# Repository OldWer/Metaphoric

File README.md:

# Metaphoric - an enhanced Oric clone
Metaphoric is an Oric clone with the memory subsystem based on the OriClone-1 project and some additional features:
* Composite video output (RCA socket)
* TRRS audio-video socket for connecting "jack to 3xRCA" cable
* Footprints for both original AY-3-8912 chips and for (much cheaper) AY-3-8910 chips (or other 40-pin clones)
* Ability to use 7905 or 7805 power regulator and also to power the Metaphoric using an external +5V power supply
* Two Atari-standard joystick ports on the keyboard PCB — one is an IJK „Stingy” port, the other is a cursors+space joystick for games that do not support IJK but are controlled with cursors or make it possible to redefine the keys.
* Easily accessible RESET and NMI buttons on top of the keyboard.
* Easily accessible switches for changing the ROM between Oric-1 and Oric Atmos and for disabling the IJK interface (it may interfere with the operation of printer port and it can also corrupt sound in games that do not support IJK, e.g. Manic Miner)
* Automatic hardware V-sync hack - original Orics did not have any way of checking the vertical sync signal, which made it difficult to write games without flickering sprites, so somebody came up with the idea of connecting video sync signal to tape in using an external cable and synchronizing games/demos in that way. Metaphoric has a transistor that connects sync out to tape in when the tape relay is inactive and disconnects it when the relay is active (to allow loading from tape).

# Building the Metaphoric
<b>Note</b>: The main PCB fits in the original Oric-1/Atmos case (the keyboard PCB <i>does not</i>!). If you would like to use the main PCB with the original keyboard and case, do not install J10 (TRRS socket) and J7 (auxiliary connector that supports the extra switches, buttons and ports on the keyboard). Also all the chips near the bottom of the board - IC10, IC15/18, IC5, IC6, IC12 and IC16 - cannot be socketed and must be soldered directly to the board, or the original case won't close.

The repository contains two directories with KiCAD projects for the main PCB and the keyboard PCB. The bill of materials is available in <i>BOM.*</i> files in the respective directories (in <i>.csv</i>, <i>.xlsx</i> and <i>.PDF</i> formats). In the <i>gerbers</i> subdirectories there are gerber files ready for manufacturing (I used recommended JLCPCB settings when exporting the gerbers). In the main PCB's <i>STL</i> subdirectory there are 3D models for a simple case and also for a spacer which you can print in 5 copies and which is used to separate the two boards. In the keyboard's <i>STL</i> subdirectory there is a 3D model for a holder that fits in the big square holes in the keyboard PCB and holds a typical space key stabilizer.

<b>Note about ROMs</b>: You can use either a 28c128 EEPROM or a 27c512 EPROM, appropriate <i>.bin</i> files are in the <i>MetaphoricV2/ROM</i> subdirectory. 27c256 EPROM would be enough to store two 16K banks with Oric-1 and Atmos ROMs, but it has different pinout - it would still work, but it wouldn't be possible to select ROM banks and only the high bank would be available. However, if you happen to have only 27c256 EPROMs, you may cut the trace between the ROM pins 27 and 28 (on the back of the PCB) and run a bodge wire from ROM pin 1 to ROM pin 27; this should make it possible to use a 27c256 EPROM with switchable banks.

Most of the build is pretty self-explanatory, as all the components are described on the PCB. The things to watch for, in no particular order, are as follows:
1. You can omit all the parts in the 'COMPOSITE VIDEO SECTION' if you're only planning to use the RGB output (well, maybe except for the TRRS socket, which can also be used to output audio, and the J11 header). The file 'RGB_Scart_Tape.pdf' shows how to build a SCART cable, and this is definitely the recommended way of using an Oric, original or cloned.
2. Next to the composite RCA socket there is the J11 header. You can put jumper on pins 2-3 to use the nearby 3.5mm TRRS socket as an audio/video video out; there are ready-made 3.5mm jack-3 x RCA cables which you can use to output video and sound. Or you can put a jumper on pins 1-2 to use the TRRS socket as a regular 3.5mm stereo sound out, useful for connecting the Oric to a stereo system or an external speaker. 
3. You can omit all the parts in the "AMPLIFIER SECTION" if you're not going to use the internal speaker. Again, highly recommended to skip these components, they were only added for the sake of completeness, the sound quality is pretty terrible with the internal speaker and in some games there is no way to turn it off or to control volume.
4. The J1 header on the right side of the board can be used to switch the ROM bank, but if the main PCB is connected to the Metaphoric keyboard PCB, it <b>should not</b> be jumpered. There is a switch on the keyboard PCB that does the same, and because switching the banks means connecting either ground or +5V to one of the ROM address lines, if you leave the J1 jumpered and then connect the Metaphoric keyboard, in one of the two switch positions the +5V will get shorted to ground. So you can install the J1 e.g. for testing the main PCB or if it is to be used in the original Oric case, but before you connect it to the Metaphoric keyboard, <b>remember to take the jumper off!</b>
5. In the power section in the top right corner of the main PCB there are footprints for either 7905 or 7805 regulator. The 7905 is recommended only if you intend to use the Metaphoric with original Oric accessories, such as floppy drives (or modern recreations, such as Cumana Reborn). Modern solutions, such as Erebus or Loci, can be used with 7805 or an external +5V power supply. Depending on which regulator you choose, you must close one of the J12/J13 bridges. Close J12 (using a piece of wire, a diode leg will do) if using 7905, close J13 if using 7805. It is also possible to connect an external power switch across one of those bridges and use it to power the Metaphoric on and off. Another way to power the Metaphoric is to close both J12 and J13 bridges (without installing any regulator!) and use external +5V power supply, <b>center positive</b> (ground on the sleeve, +5V on the tip). I personally prefer this solution (no heat generated inside) and just use a USB power supply. If you decide to use a regulator, power the Metaphoric with a +9V power supply, <b>center positive</b>.
9. The main PCB and the keyboard PCB are connected using two pin headers - J3 and J7 on the main PCB, J1 and J2 on the keyboard PCB. Two male pin headers must be installed on the back of the main PCB, two female headers on the back of the keyboard PCB, and then the two boards must be connected back to back:

Then you should put 3D printed spacers between the two boards where the holes are and screw the boards to the case using M3x16 or M3x18 screws.

10. As for the keyboard, the joystick ports must be soldered on the back side of the PCB, like so:

11. There are also solder jumpers JP2 and JP3 that can be used to configure additional joystick buttons (as in eg. MSX, Amstrad CPC or Sega Master System/Amiga joysticks). There are some powered joysticks (e.g. with an autofire function) which are usually powered from the pin 7 of the DB9 port, and it probably wouldn't be a good idea to power them intermittently from the outputs of the VIA or the AY chip. If you'd like to use additional buttons, see the note in the keyboard schematic.
12. The spacebar stabilizer holder must be printed once in normal orientation (left) and once mirrored (right), because it is not exactly symmetrical. Then the holders must be pushed into the big square holes in the kyeboard PCB (some light sanding may be necessary), and finally the stabilizer itself must be glued to the holders with a tiny amount of glue (so as not to glue together the moving plastic parts).

If in doubt, open the relevant KiCAD PCB file and go to the 3D viewer; I've added 3D models for all the parts, creating some that I could not find anywhere, and you can check exactly how everything should look like.

If you have any questions, write to me at oldwer@op.pl, I will be happy to help.

Good luck soldering your own Oric!

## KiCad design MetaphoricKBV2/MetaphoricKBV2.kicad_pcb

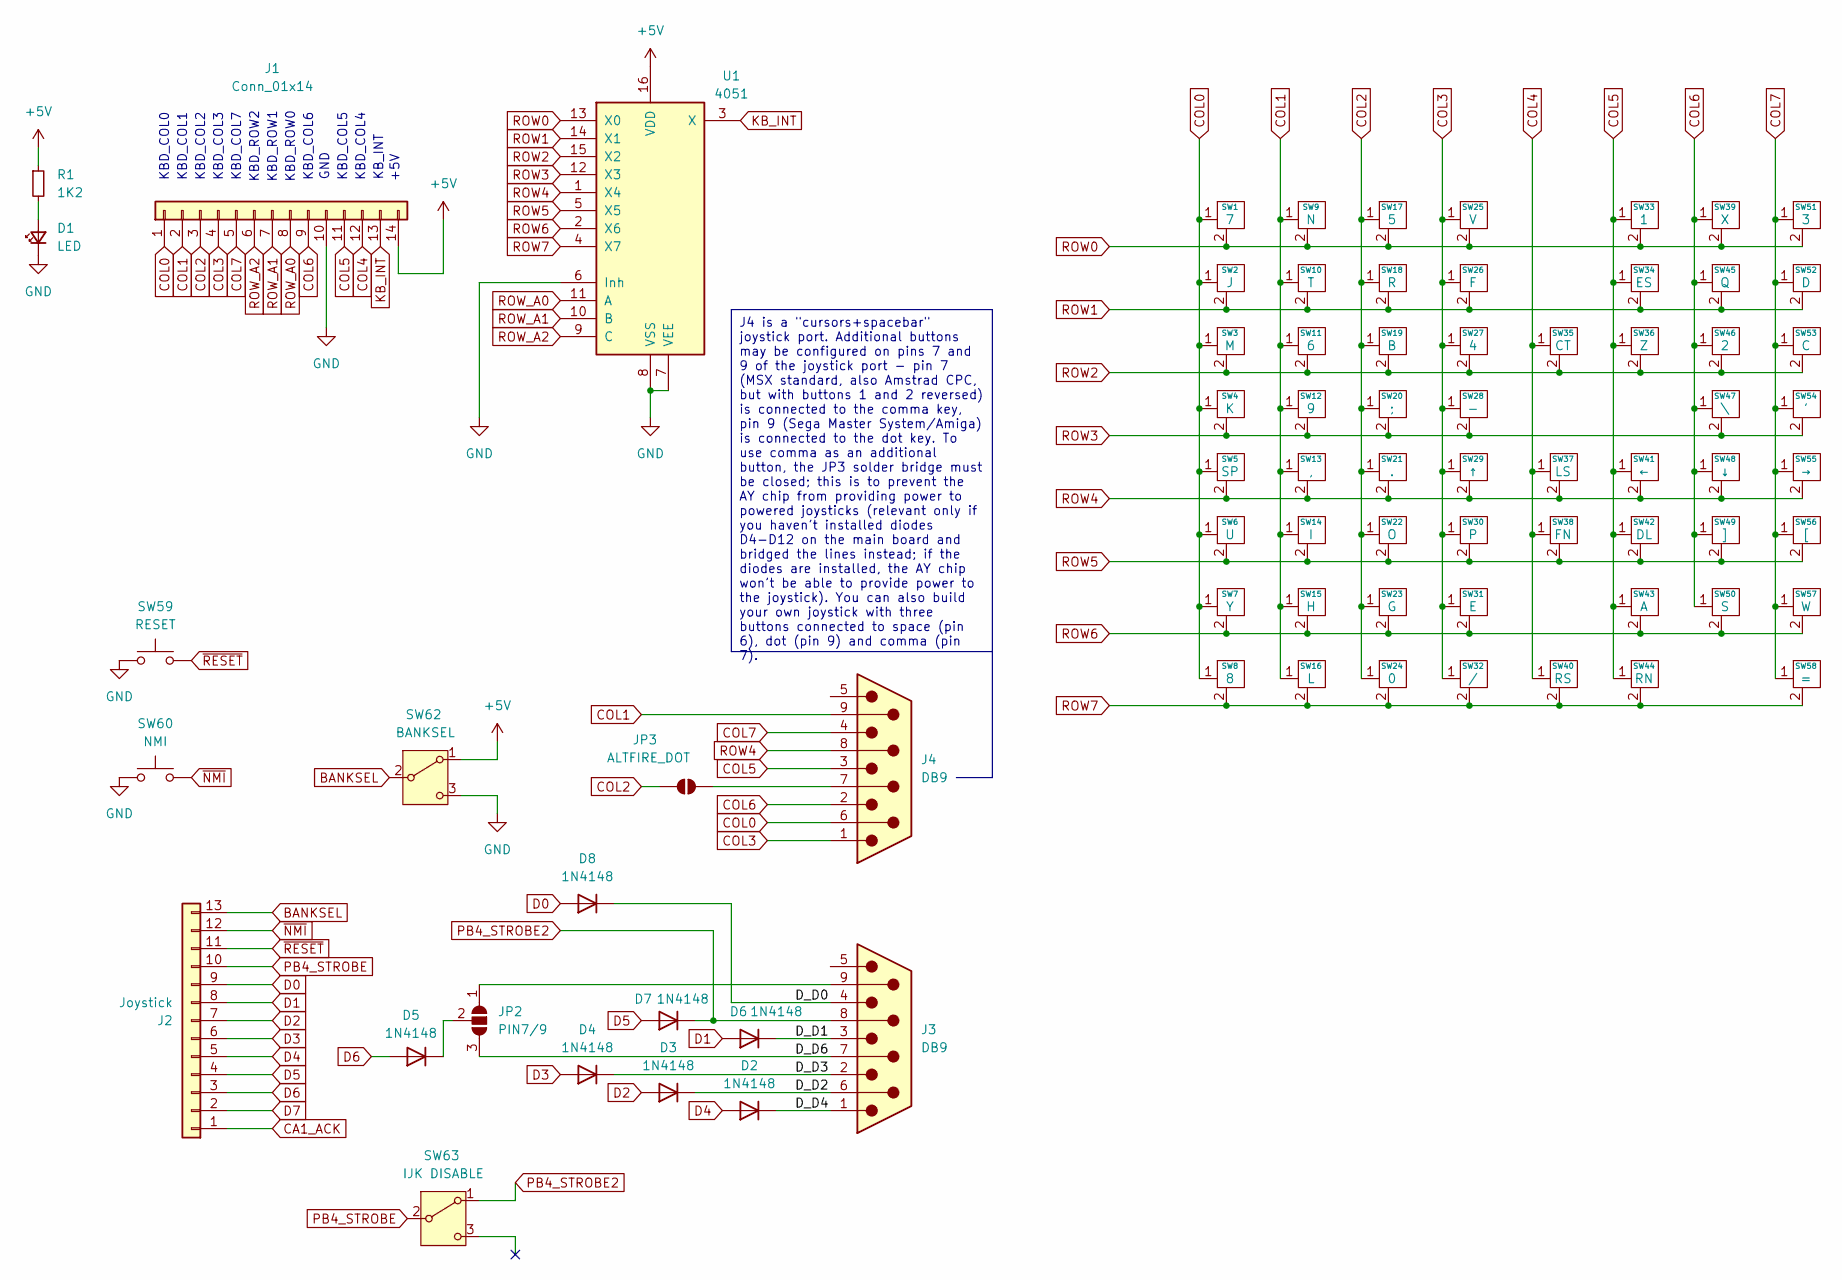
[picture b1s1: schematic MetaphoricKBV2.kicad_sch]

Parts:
D1: LED; LED_D5.0mm
D2, D3, D4, D5, D6, D7, D8: 1N4148; D_DO-35_SOD27_P7.62mm_Horizontal
J1: Conn_01x14; PinHeader_1x14_P2.54mm_Vertical
J2: Joystick; PinHeader_1x13_P2.54mm_Vertical
J3, J4: DB9; DB_9M
JP2: PIN7/9; SolderJumper-3_P1.3mm_Open_RoundedPad1.0x1.5mm
JP3: ALTFIRE_DOT; SolderJumper-2_P1.3mm_Open_RoundedPad1.0x1.5mm
R1: 1K2; R_Axial_DIN0204_L3.6mm_D1.6mm_P7.62mm_Horizontal
SW1: 7; SW_Cherry_MX_PCB_1.00u
SW2: J; SW_Cherry_MX_PCB_1.00u
SW3: M; SW_Cherry_MX_PCB_1.00u
SW4: K; SW_Cherry_MX_PCB_1.00u
SW5: SP; SW_Cherry_MX_PCB_6.25u
SW6: U; SW_Cherry_MX_PCB_1.00u
SW7: Y; SW_Cherry_MX_PCB_1.00u
SW8: 8; SW_Cherry_MX_PCB_1.00u
SW9: N; SW_Cherry_MX_PCB_1.00u
SW10: T; SW_Cherry_MX_PCB_1.00u
SW11: 6; SW_Cherry_MX_PCB_1.00u
SW12: 9; SW_Cherry_MX_PCB_1.00u
SW13: ,; SW_Cherry_MX_PCB_1.00u
SW14: I; SW_Cherry_MX_PCB_1.00u
SW15: H; SW_Cherry_MX_PCB_1.00u
SW16: L; SW_Cherry_MX_PCB_1.00u
SW17: 5; SW_Cherry_MX_PCB_1.00u
SW18: R; SW_Cherry_MX_PCB_1.00u
SW19: B; SW_Cherry_MX_PCB_1.00u
SW20: ;; SW_Cherry_MX_PCB_1.00u
SW21: .; SW_Cherry_MX_PCB_1.00u
SW22: O; SW_Cherry_MX_PCB_1.00u
SW23: G; SW_Cherry_MX_PCB_1.00u
SW24: 0; SW_Cherry_MX_PCB_1.00u
SW25: V; SW_Cherry_MX_PCB_1.00u
SW26: F; SW_Cherry_MX_PCB_1.00u
SW27: 4; SW_Cherry_MX_PCB_1.00u
SW28: -; SW_Cherry_MX_PCB_1.00u
SW29: ↑; SW_Cherry_MX_PCB_1.00u
SW30: P; SW_Cherry_MX_PCB_1.00u
SW31: E; SW_Cherry_MX_PCB_1.00u
SW32: /; SW_Cherry_MX_PCB_1.00u
SW33: 1; SW_Cherry_MX_PCB_1.00u
SW34: ES; SW_Cherry_MX_PCB_1.00u
SW35: CT; SW_Cherry_MX_PCB_1.00u
SW36: Z; SW_Cherry_MX_PCB_1.00u
SW37: LS; SW_Cherry_MX_PCB_1.50u
SW38: FN; SW_Cherry_MX_PCB_1.00u
SW39: X; SW_Cherry_MX_PCB_1.00u
SW40: RS; SW_Cherry_MX_PCB_1.50u
SW41: ←; SW_Cherry_MX_PCB_1.00u
SW42: DL; SW_Cherry_MX_PCB_1.00u
SW43: A; SW_Cherry_MX_PCB_1.00u
SW44: RN; SW_Cherry_MX_PCB_1.50u
SW45: Q; SW_Cherry_MX_PCB_1.00u
SW46: 2; SW_Cherry_MX_PCB_1.00u
SW47: \; SW_Cherry_MX_PCB_1.00u
SW48: ↓; SW_Cherry_MX_PCB_1.00u
SW49: ]; SW_Cherry_MX_PCB_1.00u
SW50: S; SW_Cherry_MX_PCB_1.00u
SW51: 3; SW_Cherry_MX_PCB_1.00u
SW52: D; SW_Cherry_MX_PCB_1.00u
SW53: C; SW_Cherry_MX_PCB_1.00u
SW54: '; SW_Cherry_MX_PCB_1.00u
SW55: →; SW_Cherry_MX_PCB_1.00u
SW56: [; SW_Cherry_MX_PCB_1.00u
SW57: W; SW_Cherry_MX_PCB_1.00u
SW58: =; SW_Cherry_MX_PCB_1.00u
SW59: RESET; SW_PUSH_6mm
SW60: NMI; SW_PUSH_6mm
SW62: BANKSEL; PinHeader_1x03_P2.54mm_Vertical
SW63: IJK DISABLE; PinHeader_1x03_P2.54mm_Vertical
U1: 4051; DIP-16_W7.62mm_LongPads

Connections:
+5V: J1.14, R1.1, SW62.1 (A), U1.16 (VDD)
/D_D0: D8.1 (K), J3.4
/D_D1: D6.1 (K), J3.3
/D_D2: D3.1 (K), J3.6
/D_D3: D4.1 (K), J3.2
/D_D4: D2.1 (K), J3.1
/D_D6: J3.7, JP2.3 (B)
BANKSEL: J2.13, SW62.2 (B)
CA1_ACK: J2.1
COL0: J1.1, J4.6, SW1.1, SW2.1, SW3.1, SW4.1, SW5.1, SW6.1, SW7.1, SW8.1
COL1: J1.2, J4.9, SW9.1, SW10.1, SW11.1, SW12.1, SW13.1, SW14.1, SW15.1, SW16.1
COL2: J1.3, JP3.1 (A), SW17.1, SW18.1, SW19.1, SW20.1, SW21.1, SW22.1, SW23.1, SW24.1
COL3: J1.4, J4.1, SW25.1, SW26.1, SW27.1, SW28.1, SW29.1, SW30.1, SW31.1, SW32.1
COL4: J1.12, SW35.1, SW37.1, SW38.1, SW40.1
COL5: J1.11, J4.3, SW33.1, SW34.1, SW36.1, SW41.1, SW42.1, SW43.1, SW44.1
COL6: J1.9, J4.2, SW39.1, SW45.1, SW46.1, SW47.1, SW48.1, SW49.1, SW50.1
COL7: J1.5, J4.4, SW51.1, SW52.1, SW53.1, SW54.1, SW55.1, SW56.1, SW57.1, SW58.1
D0: D8.2 (A), J2.9
D1: D6.2 (A), J2.8
D2: D3.2 (A), J2.7
D3: D4.2 (A), J2.6
D4: D2.2 (A), J2.5
D5: D7.2 (A), J2.4
D6: D5.2 (A), J2.3
D7: J2.2
GND: D1.1 (K), J1.10, SW59.1, SW60.1, SW62.3 (C), U1.6 (Inh), U1.7 (VEE), U1.8 (VSS)
KB_INT: J1.13, U1.3 (X)
unnamed: D1.2 (A), R1.2
unnamed: D5.1 (K), JP2.2 (C)
unnamed: J3.9, JP2.1 (A)
unnamed: J4.7, JP3.2 (B)
PB4_STROBE: J2.10, SW63.2 (B)
PB4_STROBE2: D7.1 (K), J3.8, SW63.1 (A)
ROW0: SW1.2, SW9.2, SW17.2, SW25.2, SW33.2, SW39.2, SW51.2, U1.13 (X0)
ROW1: SW2.2, SW10.2, SW18.2, SW26.2, SW34.2, SW45.2, SW52.2, U1.14 (X1)
ROW2: SW3.2, SW11.2, SW19.2, SW27.2, SW35.2, SW36.2, SW46.2, SW53.2, U1.15 (X2)
ROW3: SW4.2, SW12.2, SW20.2, SW28.2, SW47.2, SW54.2, U1.12 (X3)
ROW4: J4.8, SW5.2, SW13.2, SW21.2, SW29.2, SW37.2, SW41.2, SW48.2, SW55.2, U1.1 (X4)
ROW5: SW6.2, SW14.2, SW22.2, SW30.2, SW38.2, SW42.2, SW49.2, SW56.2, U1.5 (X5)
ROW6: SW7.2, SW15.2, SW23.2, SW31.2, SW43.2, SW50.2, SW57.2, U1.2 (X6)
ROW7: SW8.2, SW16.2, SW24.2, SW32.2, SW40.2, SW44.2, SW58.2, U1.4 (X7)
ROW_A0: J1.8, U1.11 (A)
ROW_A1: J1.7, U1.10 (B)
ROW_A2: J1.6, U1.9 (C)
~NMI: J2.12, SW60.2
~RESET: J2.11, SW59.2

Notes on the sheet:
J4 is a "cursors+spacebar" joystick port. Additional buttons may be configured on pins 7 and 9 of the joystick port - pin 7 (MSX standard, also Amstrad CPC, but with buttons 1 and 2 reversed) is connected to the comma key, pin 9 (Sega Master System/Amiga) is connected to the dot key. To use comma a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
KBD_COL0
KBD_COL2
+5V
KBD_ROW1
KBD_COL6
KBD_COL7
KBD_COL3
KBD_COL4
KB_INT
KBD_COL1
KBD_COL5
KBD_ROW0
KBD_ROW2
GND

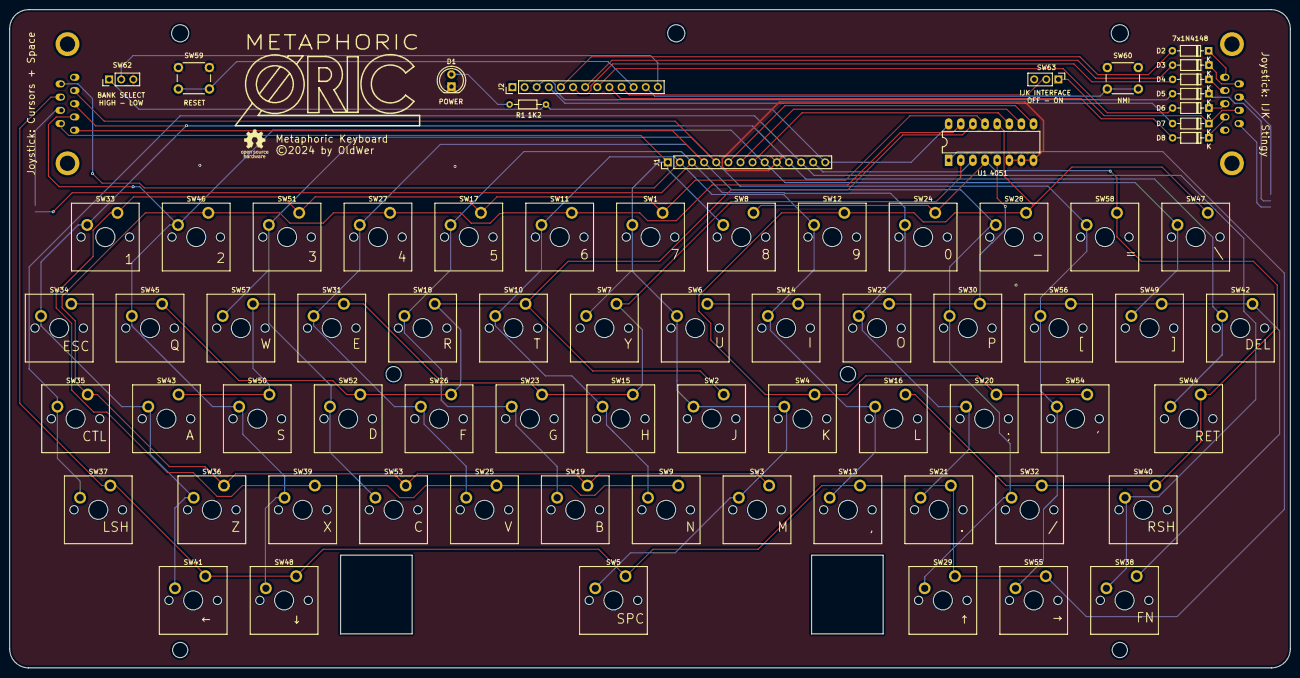
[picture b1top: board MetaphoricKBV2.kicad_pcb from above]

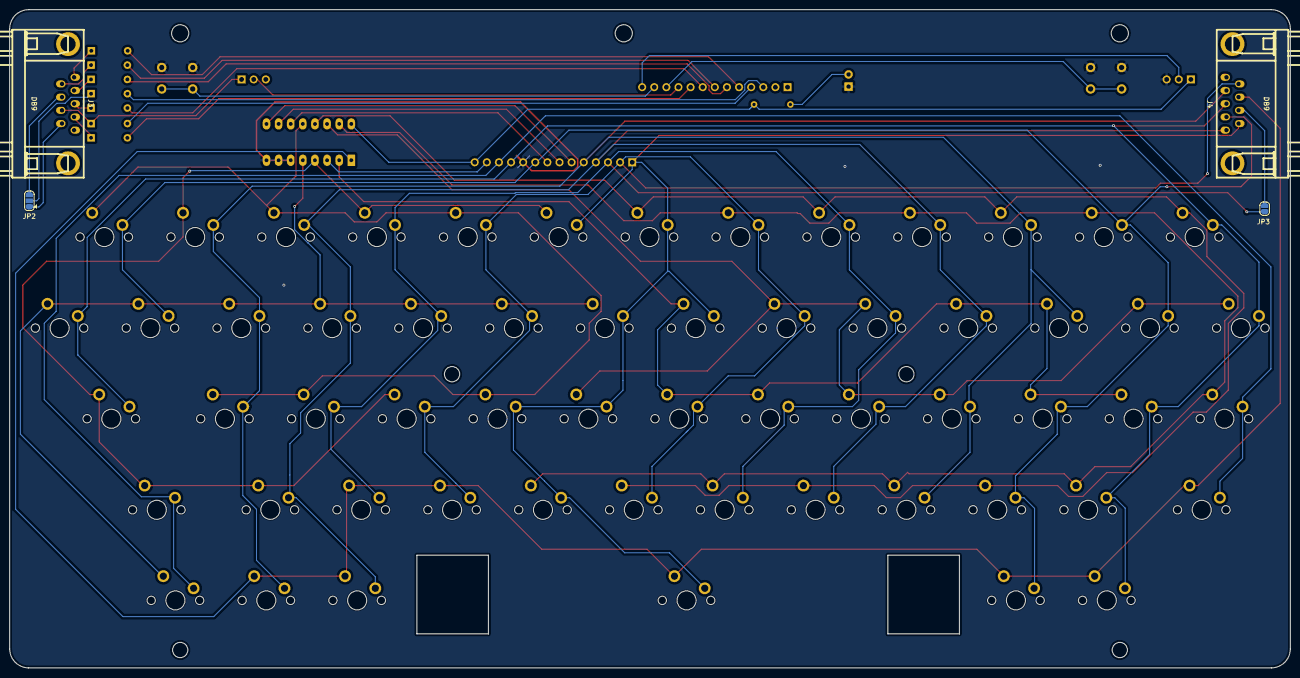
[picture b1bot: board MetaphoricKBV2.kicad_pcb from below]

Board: 2 copper layers, 268.5 x 138.0 mm, 78 parts (4 on the bottom side), 44 nets.

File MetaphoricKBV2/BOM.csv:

Reference;Value;Footprint;Qty;;;
DIODES;;;;;;
D1;LED;LED 5.0mm;1;;;
"D2;D3;D4;D5;D6;D7;D8";1N4148;DO-35;7;;;
CONNECTORS;;;;;;
J1;Conn_01x14;PinHeader_1x14 Female;1;;;
J2;Joystick;PinHeader_1x13 Female;1;;;
"J3;J4";DB9;DB-9;2;;;
RESISTOR;;;;;;
R1;1K2;Resistor;1;;;
KEY SWITCHES;;;;;;
SW1-SW58;;Cherry MX;58;;;
SWITCHES;;;;;;
SW59;RESET;Tact Switch;1;;;
SW60;NMI;Tact Switch;1;;;
SW62;BANKSEL;Switch 3pin;1;;;
SW63;IJK DISABLE;Switch 3pin;1;;;
IC;;;;;DIP Socket;
U1;4051;DIP-16;1;;DIP-16;1

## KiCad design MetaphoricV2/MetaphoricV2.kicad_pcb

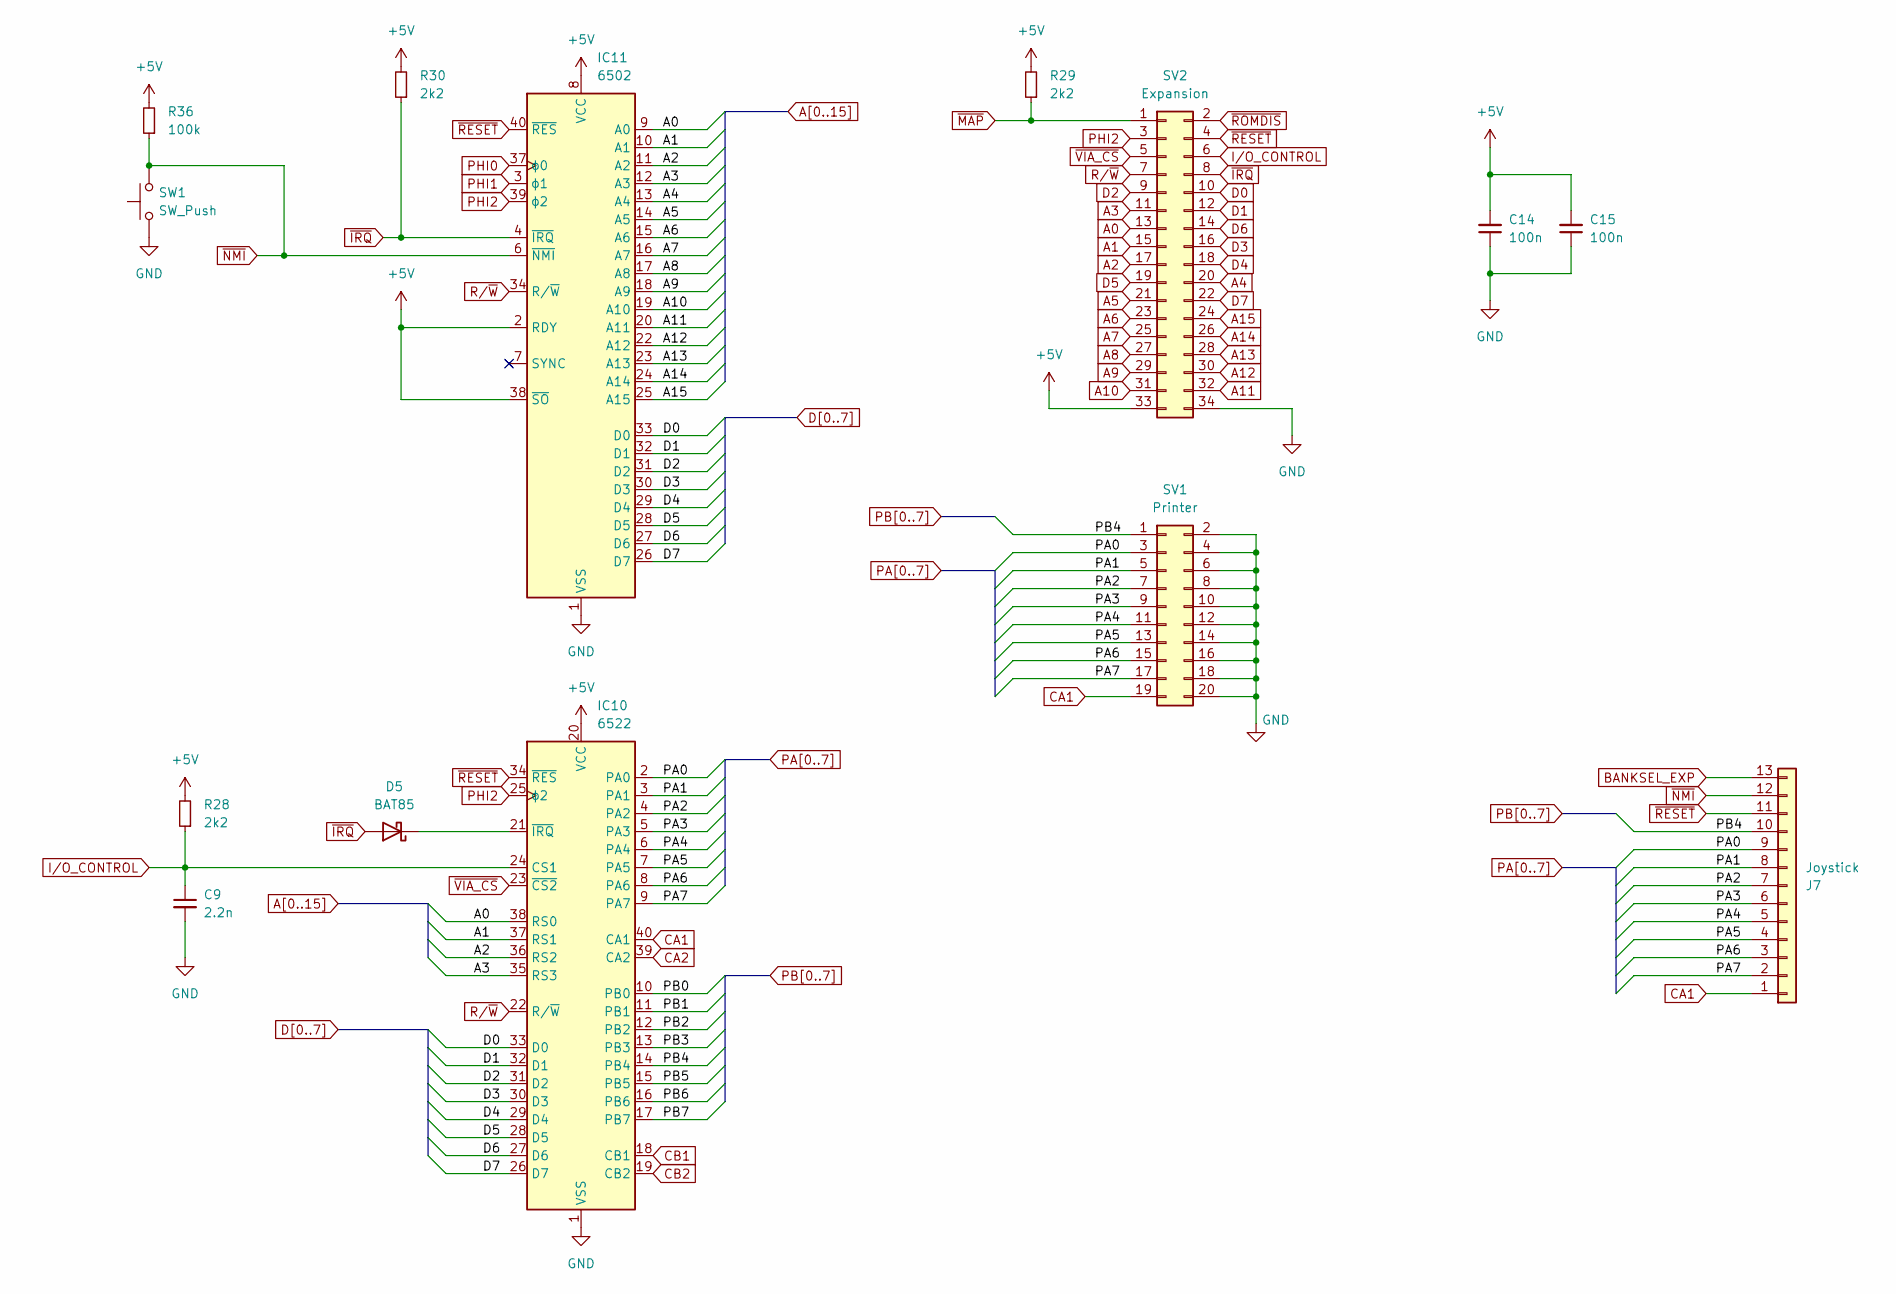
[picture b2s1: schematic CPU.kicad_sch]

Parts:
C9: 2.2n; C_Disc_D5.0mm_W2.5mm_P5.00mm
C14, C15: 100n; C_Disc_D5.0mm_W2.5mm_P5.00mm
D5: BAT85; D_DO-35_SOD27_P7.62mm_Horizontal
IC10: 6522; DIP-40_W15.24mm_LongPads
IC11: 6502; DIP-40_W15.24mm_LongPads
J7: Joystick; PinHeader_1x13_P2.54mm_Vertical
R28, R29, R30: 2k2; R_Axial_DIN0207_L6.3mm_D2.5mm_P7.62mm_Horizontal
R36: 100k; R_Axial_DIN0207_L6.3mm_D2.5mm_P7.62mm_Horizontal
SV1: Printer; IDC-Header_2x10_P2.54mm_Horizontal
SV2: Expansion; IDC-Header_2x17_P2.54mm_Horizontal
SW1: SW_Push; SW_PUSH_6mm_H4.3mm

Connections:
+5V: C14.2, C15.2, IC10.20 (VCC), IC11.2 (RDY), IC11.8 (VCC), IC11.38 (~SO), R28.2, R29.2, R30.2, R36.2, SV2.33; also elsewhere on the board
A0: IC10.38 (RS0), IC11.9 (A0), SV2.13; also elsewhere on the board
A1: IC10.37 (RS1), IC11.10 (A1), SV2.15; also elsewhere on the board
A2: IC10.36 (RS2), IC11.11 (A2), SV2.17; also elsewhere on the board
A3: IC10.35 (RS3), IC11.12 (A3), SV2.11; also elsewhere on the board
A4: IC11.13 (A4), SV2.20; also elsewhere on the board
A5: IC11.14 (A5), SV2.21; also elsewhere on the board
A6: IC11.15 (A6), SV2.23; also elsewhere on the board
A7: IC11.16 (A7), SV2.25; also elsewhere on the board
A8: IC11.17 (A8), SV2.27; also elsewhere on the board
A9: IC11.18 (A9), SV2.29; also elsewhere on the board
A10: IC11.19 (A10), SV2.31; also elsewhere on the board
A11: IC11.20 (A11), SV2.32; also elsewhere on the board
A12: IC11.22 (A12), SV2.30; also elsewhere on the board
A13: IC11.23 (A13), SV2.28; also elsewhere on the board
A14: IC11.24 (A14), SV2.26; also elsewhere on the board
A15: IC11.25 (A15), SV2.24; also elsewhere on the board
BANKSEL_EXP: J7.13; also elsewhere on the board
CA1: IC10.40 (CA1), J7.1, SV1.19
CA2: IC10.39 (CA2); also elsewhere on the board
CB1: IC10.18 (CB1); also elsewhere on the board
CB2: IC10.19 (CB2); also elsewhere on the board
D0: IC10.33 (D0), IC11.33 (D0), SV2.10; also elsewhere on the board
D1: IC10.32 (D1), IC11.32 (D1), SV2.12; also elsewhere on the board
D2: IC10.31 (D2), IC11.31 (D2), SV2.9; also elsewhere on the board
D3: IC10.30 (D3), IC11.30 (D3), SV2.16; also elsewhere on the board
D4: IC10.29 (D4), IC11.29 (D4), SV2.18; also elsewhere on the board
D5: IC10.28 (D5), IC11.28 (D5), SV2.19; also elsewhere on the board
D6: IC10.27 (D6), IC11.27 (D6), SV2.14; also elsewhere on the board
D7: IC10.26 (D7), IC11.26 (D7), SV2.22; also elsewhere on the board
GND: C9.2, C14.1, C15.1, IC10.1 (VSS), IC11.1 (VSS), IC11.21 (VSS), SV1.2, SV1.4, SV1.6, SV1.8, SV1.10, SV1.12, SV1.14, SV1.16, SV1.18, SV1.20, SV2.34, SW1.1; also elsewhere on the board
I/O_CONTROL: C9.1, IC10.24 (CS1), R28.1, SV2.6
unnamed: D5.1 (K), IC10.21 (~IRQ)
PA0: IC10.2 (PA0), J7.9, SV1.3; also elsewhere on the board
PA1: IC10.3 (PA1), J7.8, SV1.5; also elsewhere on the board
PA2: IC10.4 (PA2), J7.7, SV1.7; also elsewhere on the board
PA3: IC10.5 (PA3), J7.6, SV1.9; also elsewhere on the board
PA4: IC10.6 (PA4), J7.5, SV1.11; also elsewhere on the board
PA5: IC10.7 (PA5), J7.4, SV1.13; also elsewhere on the board
PA6: IC10.8 (PA6), J7.3, SV1.15; also elsewhere on the board
PA7: IC10.9 (PA7), J7.2, SV1.17; also elsewhere on the board
PB0: IC10.10 (PB0); also elsewhere on the board
PB1: IC10.11 (PB1); also elsewhere on the board
PB2: IC10.12 (PB2); also elsewhere on the board
PB3: IC10.13 (PB3); also elsewhere on the board
PB4: IC10.14 (PB4), J7.10, SV1.1
PB5: IC10.15 (PB5); also elsewhere on the board
PB6: IC10.16 (PB6); also elsewhere on the board
PB7: IC10.17 (PB7); also elsewhere on the board
PHI0: IC11.37 (ϕ0); also elsewhere on the board
PHI1: IC11.3 (ϕ1); also elsewhere on the board
PHI2: IC10.25 (ϕ2), IC11.39 (ϕ2), SV2.3; also elsewhere on the board
R/~W: IC10.22 (R/~W), IC11.34 (R/~W), SV2.7; also elsewhere on the board
~IRQ: D5.2 (A), IC11.4 (~IRQ), R30.1, SV2.8
~MAP: R29.1, SV2.1; also elsewhere on the board
~NMI: IC11.6 (~NMI), J7.12, R36.1, SW1.2
~RESET: IC10.34 (~RES), IC11.40 (~RES), J7.11, SV2.4; also elsewhere on the board
~ROMDIS: SV2.2; also elsewhere on the board
~VIA_CS: IC10.23 (~CS2), SV2.5; also elsewhere on the board

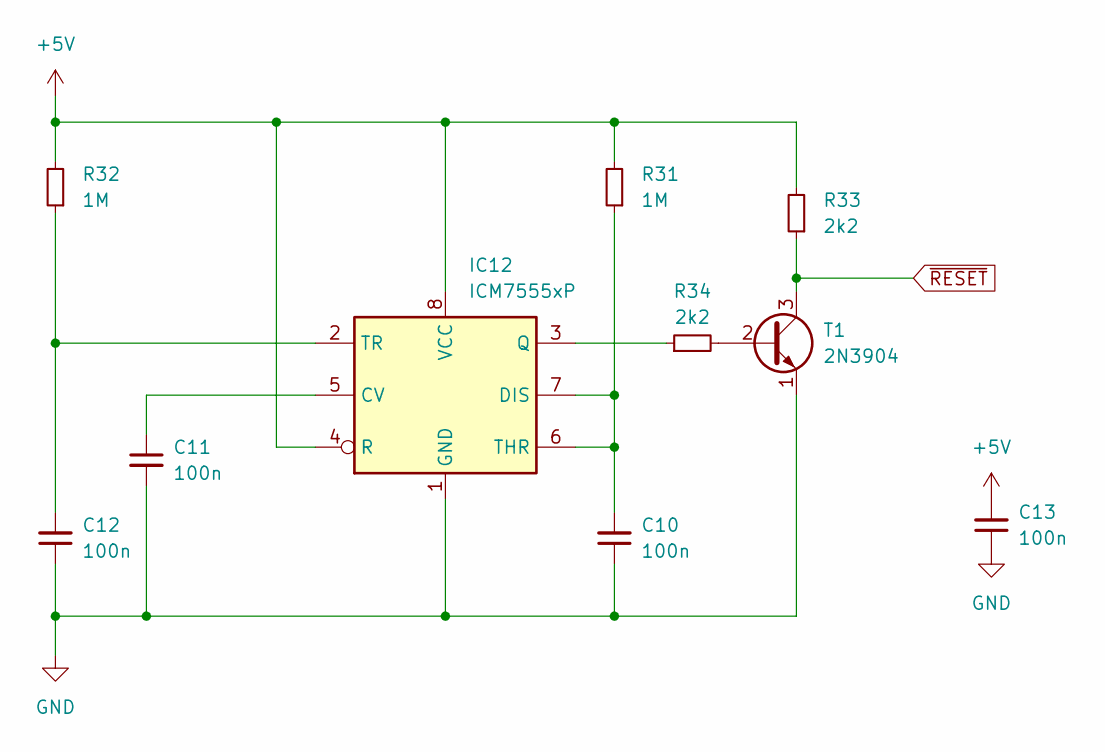
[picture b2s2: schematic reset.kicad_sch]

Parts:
C10, C11, C12, C13: 100n; C_Disc_D5.0mm_W2.5mm_P5.00mm
IC12: ICM7555xP; DIP-8_W7.62mm
R31, R32: 1M; R_Axial_DIN0207_L6.3mm_D2.5mm_P7.62mm_Horizontal
R33, R34: 2k2; R_Axial_DIN0207_L6.3mm_D2.5mm_P7.62mm_Horizontal
T1: 2N3904; TO-92_Inline

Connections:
+5V: C13.2, IC12.4 (R), IC12.8 (VCC), R31.2, R32.2, R33.2; also elsewhere on the board
GND: C10.1, C11.2, C12.1, C13.1, IC12.1 (GND), T1.1 (E); also elsewhere on the board
unnamed: C11.1, IC12.5 (CV)
unnamed: C10.2, IC12.6 (THR), IC12.7 (DIS), R31.1
unnamed: IC12.3 (Q), R34.1
unnamed: C12.2, IC12.2 (TR), R32.1
unnamed: R34.2, T1.2 (B)
~RESET: R33.1, T1.3 (C); also elsewhere on the board

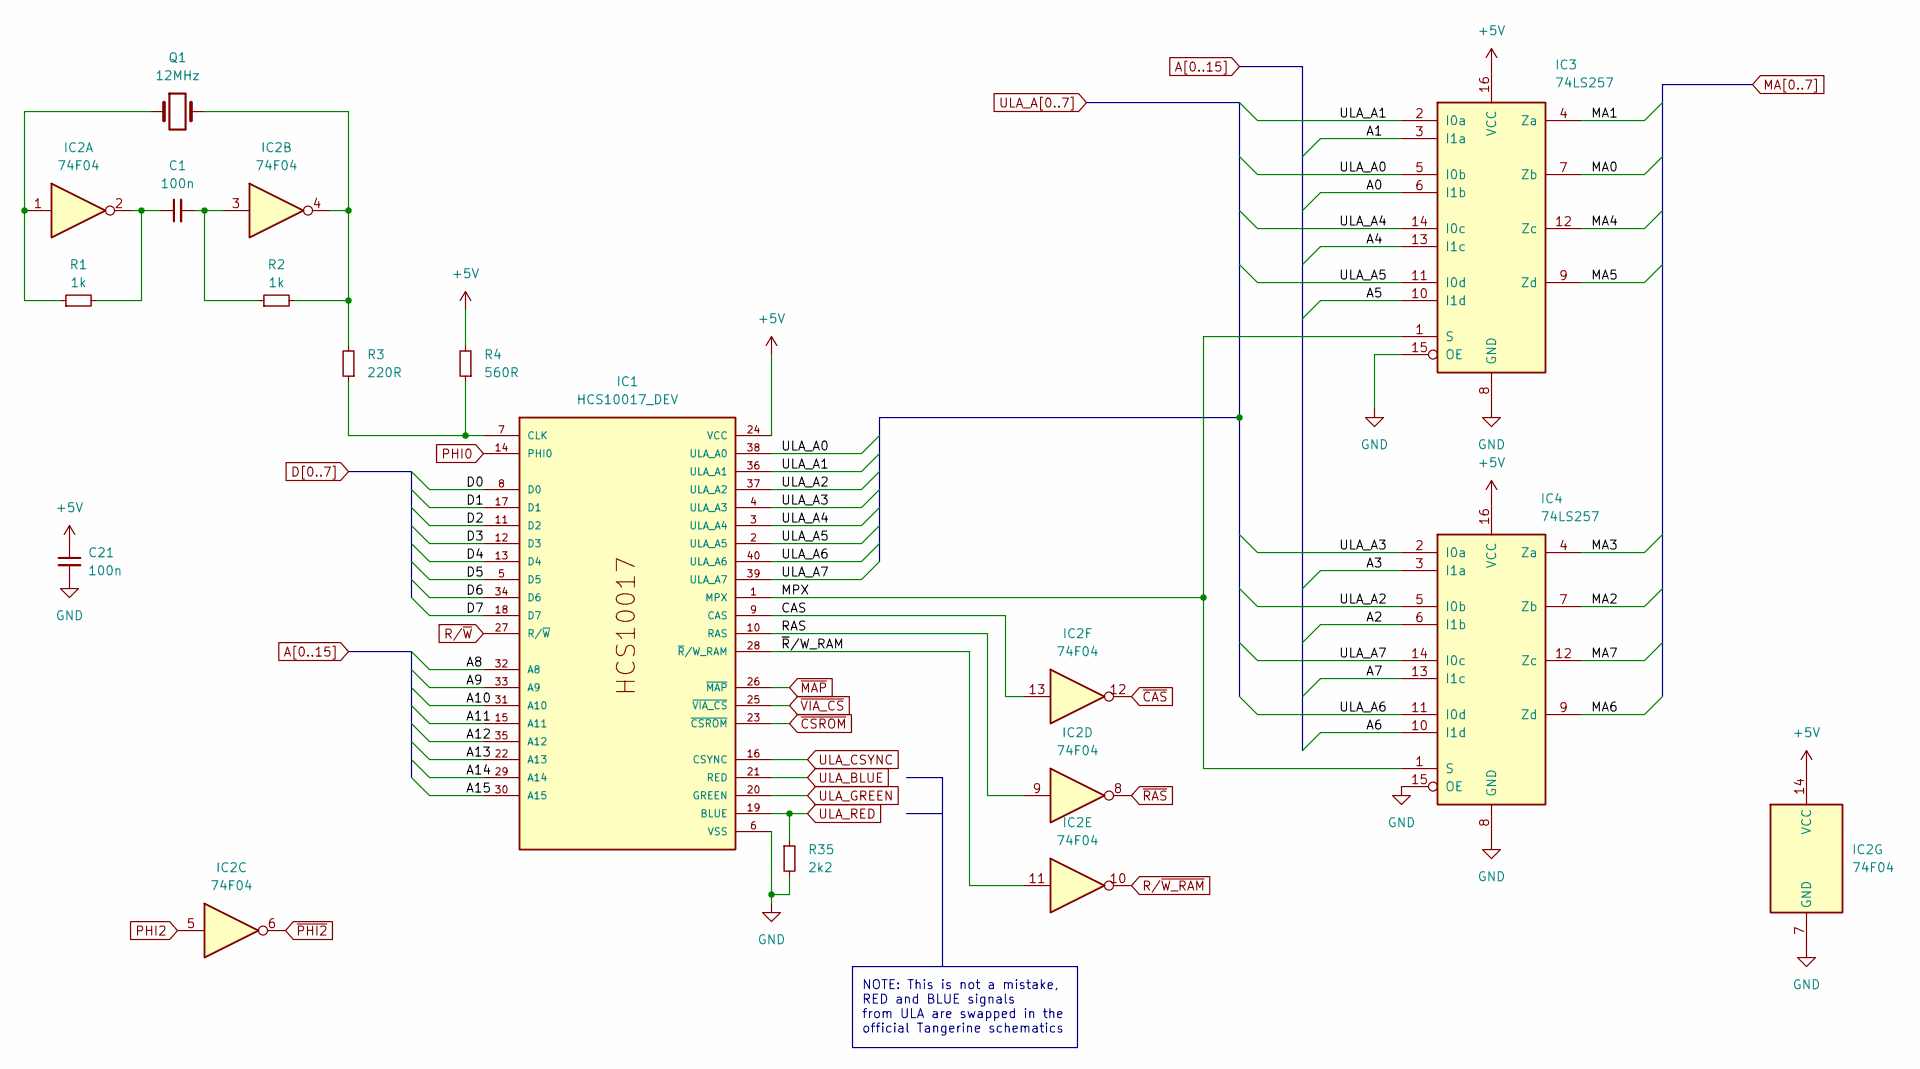
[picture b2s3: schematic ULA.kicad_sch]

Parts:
C1, C21: 100n; C_Disc_D5.0mm_W2.5mm_P5.00mm
IC1: HCS10017_DEV; DIP-40_W15.24mm_LongPads
IC2: 74F04; DIP-14_W7.62mm_LongPads
IC3, IC4: 74LS257; DIP-16_W7.62mm_LongPads
Q1: 12MHz; Crystal_HC49-4H_Vertical
R1, R2: 1k; R_Axial_DIN0207_L6.3mm_D2.5mm_P7.62mm_Horizontal
R3: 220R; R_Axial_DIN0207_L6.3mm_D2.5mm_P7.62mm_Horizontal
R4: 560R; R_Axial_DIN0207_L6.3mm_D2.5mm_P7.62mm_Horizontal
R35: 2k2; R_Axial_DIN0207_L6.3mm_D2.5mm_P7.62mm_Horizontal

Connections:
+5V: C21.1, IC1.24 (VCC), IC2.14 (VCC), IC3.16 (VCC), IC4.16 (VCC), R4.2; also elsewhere on the board
/ULA/CAS: IC1.9 (CAS), IC2.13
/ULA/MPX: IC1.1 (MPX), IC3.1 (S), IC4.1 (S)
/ULA/RAS: IC1.10 (RAS), IC2.9
/ULA/~R/W_RAM: IC1.28 (~R/W_RAM), IC2.11
A0: IC3.6 (I1b); also elsewhere on the board
A1: IC3.3 (I1a); also elsewhere on the board
A2: IC4.6 (I1b); also elsewhere on the board
A3: IC4.3 (I1a); also elsewhere on the board
A4: IC3.13 (I1c); also elsewhere on the board
A5: IC3.10 (I1d); also elsewhere on the board
A6: IC4.10 (I1d); also elsewhere on the board
A7: IC4.13 (I1c); also elsewhere on the board
A8: IC1.32 (A8); also elsewhere on the board
A9: IC1.33 (A9); also elsewhere on the board
A10: IC1.31 (A10); also elsewhere on the board
A11: IC1.15 (A11); also elsewhere on the board
A12: IC1.35 (A12); also elsewhere on the board
A13: IC1.22 (A13); also elsewhere on the board
A14: IC1.29 (A14); also elsewhere on the board
A15: IC1.30 (A15); also elsewhere on the board
D0: IC1.8 (D0); also elsewhere on the board
D1: IC1.17 (D1); also elsewhere on the board
D2: IC1.11 (D2); also elsewhere on the board
D3: IC1.12 (D3); also elsewhere on the board
D4: IC1.13 (D4); also elsewhere on the board
D5: IC1.5 (D5); also elsewhere on the board
D6: IC1.34 (D6); also elsewhere on the board
D7: IC1.18 (D7); also elsewhere on the board
GND: C21.2, IC1.6 (VSS), IC2.7 (GND), IC3.8 (GND), IC3.15 (OE), IC4.8 (GND), IC4.15 (OE), R35.2; also elsewhere on the board
MA0: IC3.7 (Zb); also elsewhere on the board
MA1: IC3.4 (Za); also elsewhere on the board
MA2: IC4.7 (Zb); also elsewhere on the board
MA3: IC4.4 (Za); also elsewhere on the board
MA4: IC3.12 (Zc); also elsewhere on the board
MA5: IC3.9 (Zd); also elsewhere on the board
MA6: IC4.9 (Zd); also elsewhere on the board
MA7: IC4.12 (Zc); also elsewhere on the board
unnamed: C1.1, IC2.2, R1.2
unnamed: C1.2, IC2.3, R2.1
unnamed: IC1.7 (CLK), R3.1, R4.1
unnamed: IC2.1, Q1.1, R1.1
unnamed: IC2.4, Q1.2, R2.2, R3.2
PHI0: IC1.14 (PHI0); also elsewhere on the board
PHI2: IC2.5; also elsewhere on the board
R/~W_RAM: IC2.10; also elsewhere on the board
R/~W: IC1.27 (R/~W); also elsewhere on the board
ULA_A0: IC1.38 (ULA_A0), IC3.5 (I0b)
ULA_A1: IC1.36 (ULA_A1), IC3.2 (I0a)
ULA_A2: IC1.37 (ULA_A2), IC4.5 (I0b)
ULA_A3: IC1.4 (ULA_A3), IC4.2 (I0a)
ULA_A4: IC1.3 (ULA_A4), IC3.14 (I0c)
ULA_A5: IC1.2 (ULA_A5), IC3.11 (I0d)
ULA_A6: IC1.40 (ULA_A6), IC4.11 (I0d)
ULA_A7: IC1.39 (ULA_A7), IC4.14 (I0c)
ULA_BLUE: IC1.21 (RED); also elsewhere on the board
ULA_CSYNC: IC1.16 (CSYNC); also elsewhere on the board
ULA_GREEN: IC1.20 (GREEN); also elsewhere on the board
ULA_RED: IC1.19 (BLUE), R35.1; also elsewhere on the board
~CAS: IC2.12; also elsewhere on the board
~CSROM: IC1.23 (~CSROM); also elsewhere on the board
~MAP: IC1.26 (~MAP); also elsewhere on the board
~PHI2: IC2.6; also elsewhere on the board
~RAS: IC2.8; also elsewhere on the board
~VIA_CS: IC1.25 (~VIA_CS); also elsewhere on the board

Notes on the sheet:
NOTE: This is not a mistake, RED and BLUE signals from ULA are swapped in the official Tangerine schematics

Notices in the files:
MetaphoricKBV2/MetaphoricKBV2.kicad_pcb:
©2024 by OldWer
